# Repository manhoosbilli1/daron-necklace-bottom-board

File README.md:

# Daron_necklace_bottom

Bottom half of wearable LED necklace - power, haptic, USB-C charging

## At a Glance

- **Status**: Routed
- **Board size**: 20 x 20 mm
- **Layers**: 2
- **Components**: 42
- **Key ICs**:
  - U1: MCP73831-2-MC
  - U2: FH35C-11S-0.3SHW(50)_C7427016
  - U3: TPS63070RNMR
  - U7: DRV2605LDGS

## Schematic

Full PDF: [reports/schematic.pdf](reports/schematic.pdf)

## Component Roles

- **TPS63070RNMR** (U3) - buck-boost regulator (3.3 V output); handles wide LiPo voltage swing
- **DRV2605LDGS** (U7) - haptic motor driver for tactile feedback
- **MCP73831-2-MC** (U1) - single-cell LiPo charger
- **AO3401A** (Q1) - P-channel MOSFET for power switching / load enable
- **DMG3414U** (Q3) - N-channel MOSFET (companion to Q1 for full PowerPath)
- **FH35C-11S-0.3SHW** (U2) - 0.3 mm-pitch FPC connector for the top-board flex link
- **TC-005** (USB1) - micro USB-C receptacle (compact variant)
- **SP0503BAHT** (D1) - 3-line ESD protection on USB data lines
- **KT-0603R** (D3) - status LED

> Companion to the top-board (LED-driving half). The top board handles the addressable LED chain; this board handles power, charging, haptics.

## PCB

**Top copper**

**Bottom copper**

## Bill of Materials

| Refs | Value | Footprint | Qty | MPN | LCSC |
|------|-------|-----------|----:|-----|------|
| C1 | 47uF | PCM_JLCPCB:C_0805 | 1 |  | [C16780](https://www.lcsc.com/product-detail/_C16780.html) |
| C2,C8-C10,C15 | 100nF | PCM_JLCPCB:C_0402 | 5 |  | [C1525](https://www.lcsc.com/product-detail/_C1525.html) |
| C3,C4,C16 | 10uF | PCM_JLCPCB:C_0805 | 3 |  | [C15850](https://www.lcsc.com/product-detail/_C15850.html) |
| C5-C7 | 22uF | PCM_JLCPCB:C_0805 | 3 |  | [C45783](https://www.lcsc.com/product-detail/_C45783.html) |
| C11,C17 | 4.7uF | Capacitor_SMD:C_0402_1005Metric | 2 |  |  |
| C21,C22 | 1uF | Capacitor_SMD:C_0402_1005Metric | 2 |  |  |
| D1 | SP0503BAHT | Package_SON:WSON-6-1EP_2x2mm_P0.65mm_EP1x1.6mm | 1 |  |  |
| D2 | White | PCM_JLCPCB:D_0603 | 1 |  | [C2290](https://www.lcsc.com/product-detail/_C2290.html) |
| D3 | KT-0603R | LED_SMD:LED_0201_0603Metric | 1 |  |  |
| D4 | B5819W | Diode_SMD:D_0603_1608Metric | 1 |  |  |
| J2,J4 | Conn_01x02 | Connector_Wire:SolderWire-0.1sqmm_1x02_P3.6mm_D0.4mm_OD1mm | 2 |  |  |
| L2 | 1.5uH | Inductor_SMD:L_Coilcraft_XAL4020-XXX | 1 |  |  |
| Q1 | AO3401A | PCM_JLCPCB:Q_SOT-23 | 1 |  | [C15127](https://www.lcsc.com/product-detail/_C15127.html) |
| Q3 | DMG3414U | Package_TO_SOT_SMD:SOT-23 | 1 |  |  |
| R1 | 470kΩ | PCM_JLCPCB:R_0402 | 1 |  | [C25790](https://www.lcsc.com/product-detail/_C25790.html) |
| R2 | 150kΩ | PCM_JLCPCB:R_0402 | 1 |  | [C25755](https://www.lcsc.com/product-detail/_C25755.html) |
| R3,R4 | 5.1kΩ | PCM_JLCPCB:R_0402 | 2 |  | [C25905](https://www.lcsc.com/product-detail/_C25905.html) |
| R5 | 2.2kΩ | PCM_JLCPCB:R_0402 | 1 |  | [C25879](https://www.lcsc.com/product-detail/_C25879.html) |
| R6,R20 | 2.2k | Resistor_SMD:R_0402_1005Metric | 2 |  |  |
| R11 | 10kΩ | PCM_JLCPCB:R_0402 | 1 |  | [C25744](https://www.lcsc.com/product-detail/_C25744.html) |
| R13 | 1k | Resistor_SMD:R_0402_1005Metric | 1 |  |  |
| R14 | 10k | Resistor_SMD:R_0402_1005Metric | 1 |  |  |
| R18 | 100k | Resistor_SMD:R_0402_1005Metric | 1 |  |  |
| R19 | 100kΩ | PCM_JLCPCB:R_0402 | 1 |  | [C25741](https://www.lcsc.com/product-detail/_C25741.html) |
| U1 | MCP73831-2-MC | Package_DFN_QFN:DFN-8-1EP_3x2mm_P0.5mm_EP1.7x1.4mm | 1 |  |  |
| U2 | FH35C-11S-0.3SHW(50)_C7427016 | FH35C_11S_0_3SHW_50_:FPC-SMD_FH35C-11S-0.3SHW | 1 |  |  |
| U3 | TPS63070RNMR | TPS63070RNMR:VREG_TPS63070RNMR | 1 |  |  |
| U7 | DRV2605LDGS | Package_SO:VSSOP-10_3x3mm_P0.5mm | 1 |  |  |
| USB1 | TC-005_C6332285 | usbc:USB-C-SMD_TC-005 | 1 |  |  |

_17 of 29 line items don't have an LCSC code in the schematic - search [LCSC](https://www.lcsc.com/) or [JLC parts search](https://jlcsearch.tscircuit.com/) by MPN or footprint when sourcing._

## Files

- `Daron_necklace_bottom.kicad_pro` - KiCad project
- `Daron_necklace_bottom.kicad_sch` - schematic source
- `Daron_necklace_bottom.kicad_pcb` - PCB layout source
- `reports/schematic.pdf` - full schematic (printable)
- `reports/bom.csv` - bill of materials
- `reports/pcb-top.svg`, `reports/pcb-bottom.svg` - copper artwork
- `reports/board-stats.json` - KiCad-generated board statistics

---

_Renders and metadata auto-generated by `Backup-KiCadProject.ps1` using KiCad 10.0._

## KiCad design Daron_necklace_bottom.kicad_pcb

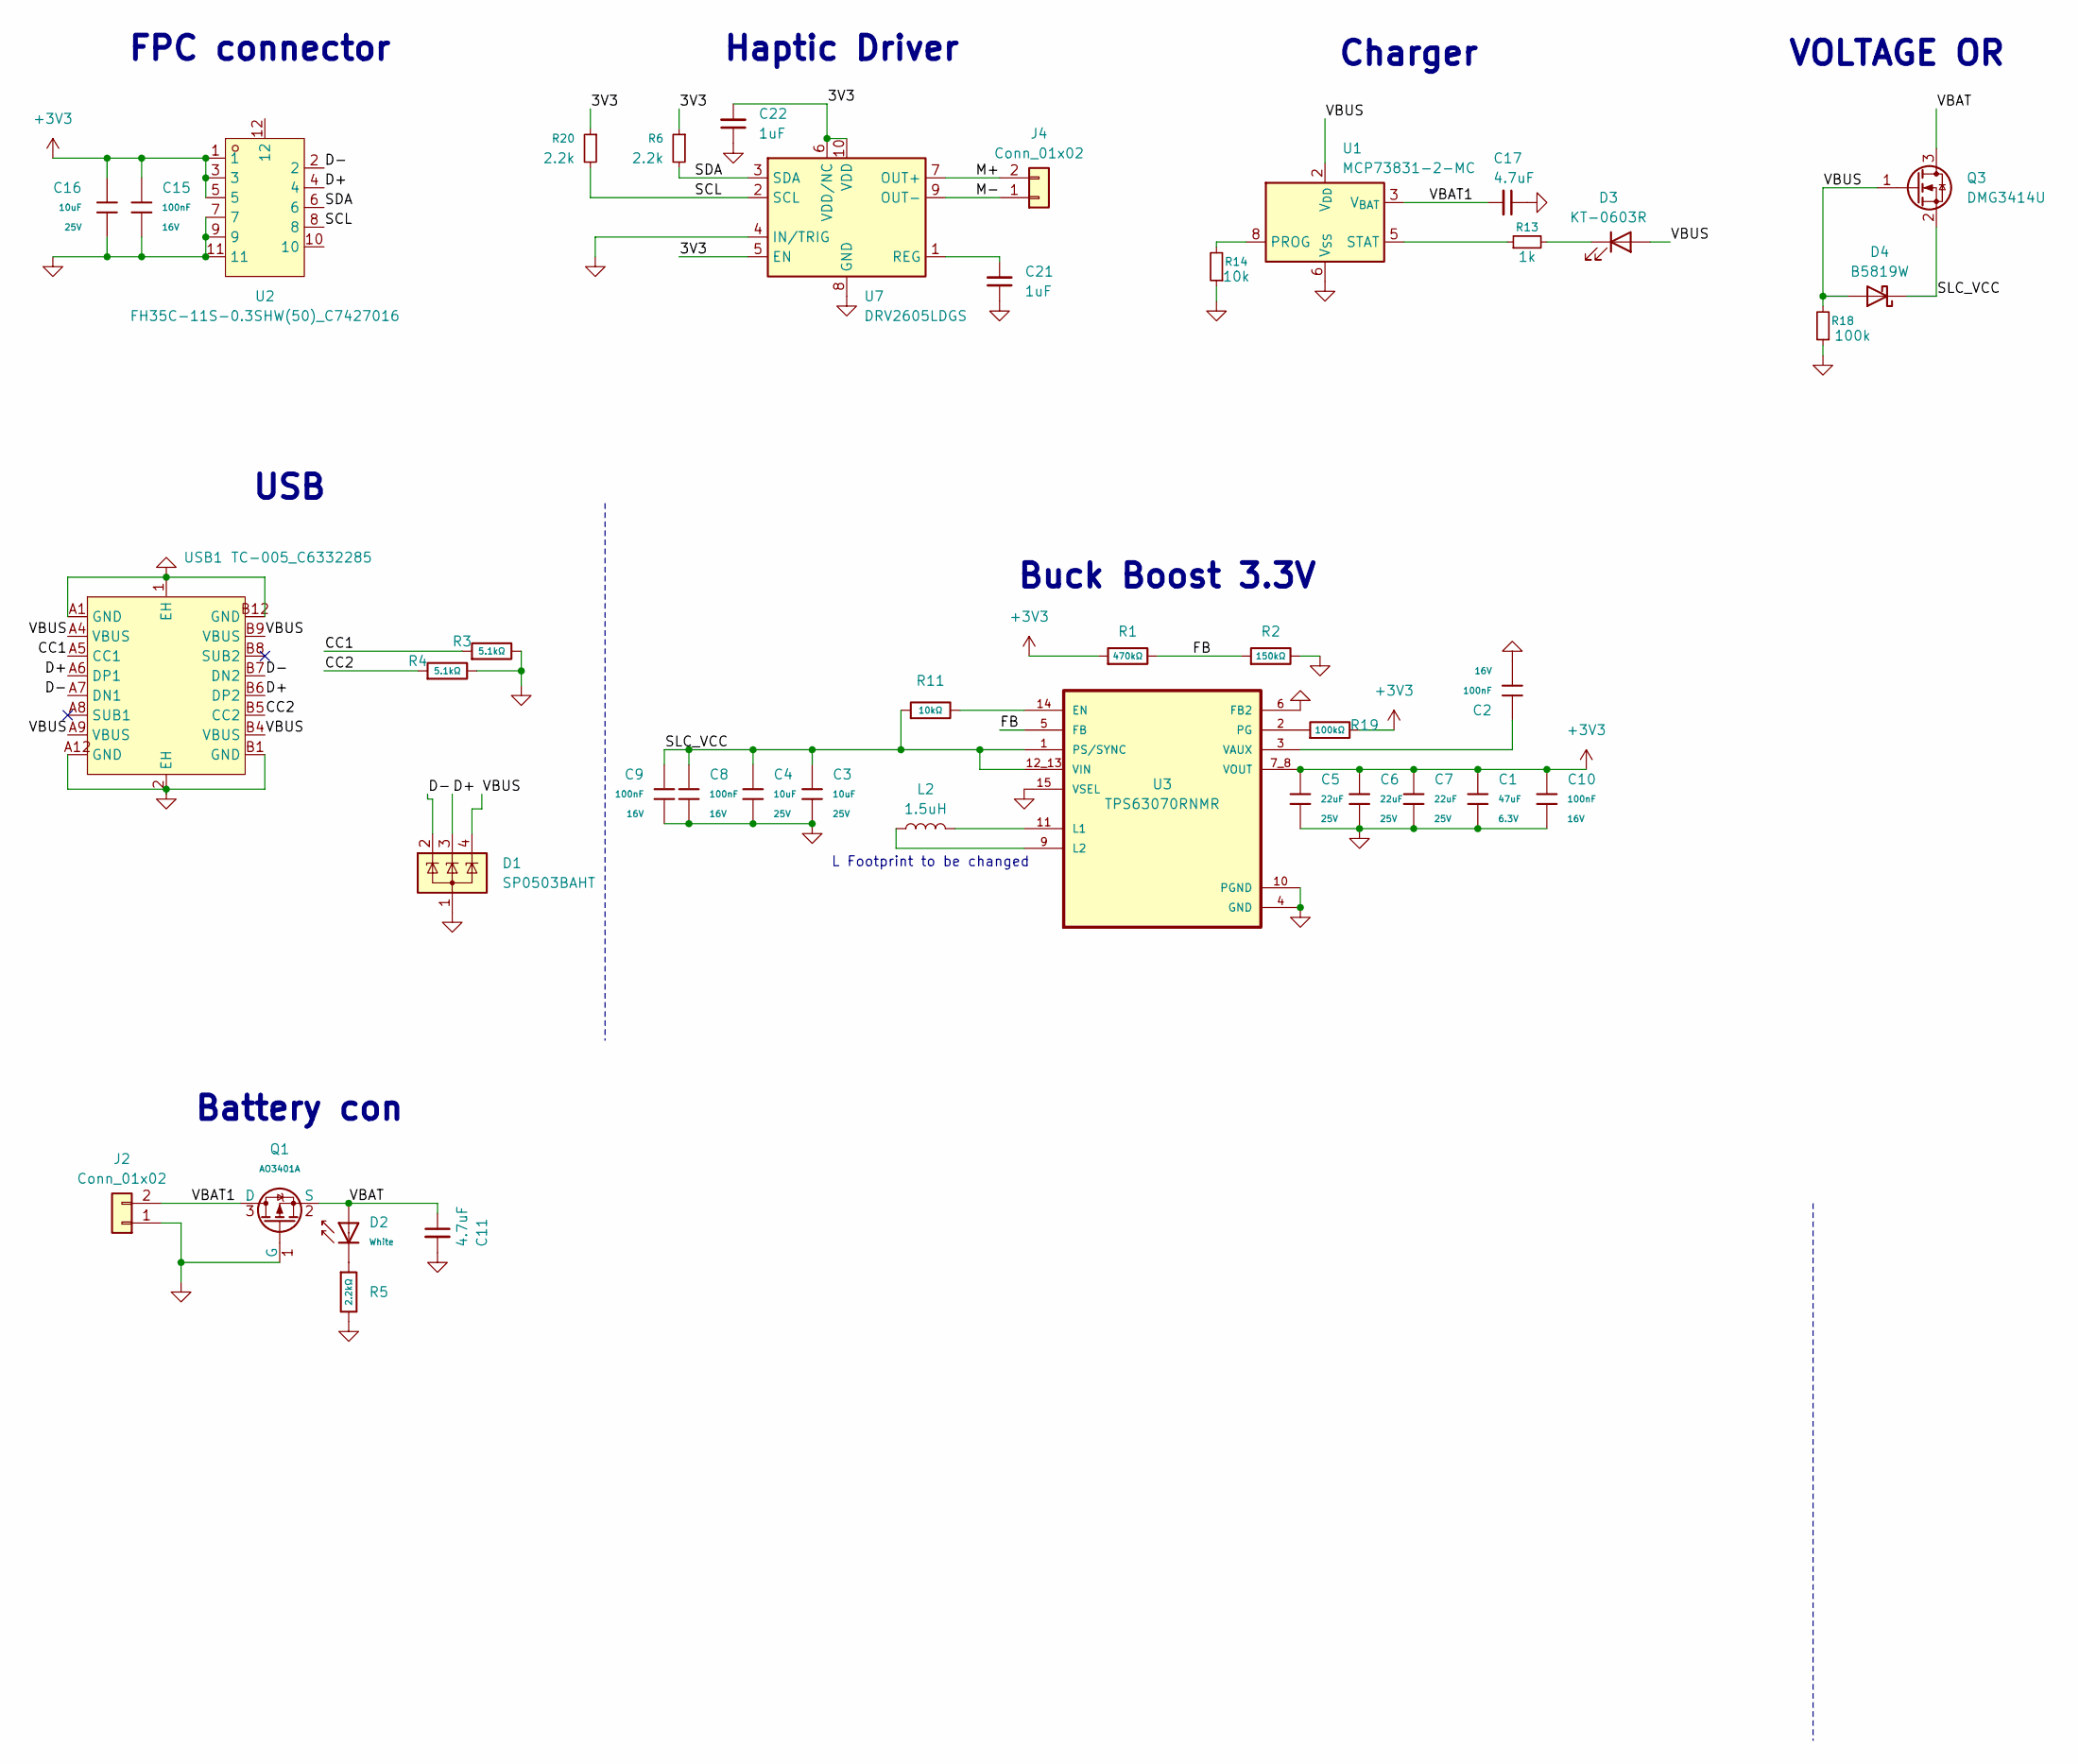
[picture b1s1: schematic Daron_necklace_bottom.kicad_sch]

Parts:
C1: 47uF; C_0805; Voltage Rated 6.3V; Tolerance ±20%; Part CL21A476MQYNNNE; LCSC C16780
C2, C8, C9, C10, C15: 100nF; C_0402; Voltage Rated 16V; Tolerance ±10%; Part CL05B104KO5NNNC; LCSC C1525
C3, C4, C16: 10uF; C_0805; Voltage Rated 25V; Tolerance ±10%; Part CL21A106KAYNNNE; LCSC C15850
C5, C6, C7: 22uF; C_0805; Voltage Rated 25V; Tolerance ±20%; Part CL21A226MAQNNNE; LCSC C45783
C11, C17: 4.7uF; C_0402_1005Metric
C21, C22: 1uF; C_0402_1005Metric
D1: SP0503BAHT; WSON-6-1EP_2x2mm_P0.65mm_EP1x1.6mm
D2: White; D_0603; Part KT-0603W; LCSC C2290
D3: KT-0603R; LED_0201_0603Metric
D4: B5819W; D_0603_1608Metric
J2, J4: Conn_01x02; SolderWire-0.1sqmm_1x02_P3.6mm_D0.4mm_OD1mm
L2: 1.5uH; L_Coilcraft_XAL4020-XXX
Q1: AO3401A; Q_SOT-23; Part AO3401A; LCSC C15127
Q3: DMG3414U; SOT-23
R1: 470kΩ; R_0402; Overload Voltage (Max) 50V; Tolerance ±1%; Part 0402WGF4703TCE; LCSC C25790
R2: 150kΩ; R_0402; Overload Voltage (Max) 50V; Tolerance ±1%; Part 0402WGF1503TCE; LCSC C25755
R3, R4: 5.1kΩ; R_0402; Overload Voltage (Max) 50V; Tolerance ±1%; Part 0402WGF5101TCE; LCSC C25905
R5: 2.2kΩ; R_0402; Overload Voltage (Max) 50V; Tolerance ±1%; Part 0402WGF2201TCE; LCSC C25879
R6, R20: 2.2k; R_0402_1005Metric
R11: 10kΩ; R_0402; Overload Voltage (Max) 50V; Tolerance ±1%; Part 0402WGF1002TCE; LCSC C25744
R13: 1k; R_0402_1005Metric
R14: 10k; R_0402_1005Metric
R18: 100k; R_0402_1005Metric
R19: 100kΩ; R_0402; Overload Voltage (Max) 50V; Tolerance ±1%; Part 0402WGF1003TCE; LCSC C25741
U1: MCP73831-2-MC; DFN-8-1EP_3x2mm_P0.5mm_EP1.7x1.4mm
U2: FH35C-11S-0.3SHW(50)_C7427016; FPC-SMD_FH35C-11S-0.3SHW; LCSC Part C7427016
U3: TPS63070RNMR; VREG_TPS63070RNMR
U7: DRV2605LDGS; VSSOP-10_3x3mm_P0.5mm
USB1: TC-005_C6332285; USB-C-SMD_TC-005; LCSC Part C6332285

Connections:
+3V3: C1.1, C5.1, C6.1, C7.1, C10.1, C15.1, C16.1, R1.1, R19.2, U2.1, U2.3, U2.5, U3.7_8 (VOUT)
/3V3: C22.2, R6.1, R20.1, U7.5 (EN), U7.6 (VDD/NC), U7.10 (VDD)
/CC1: R3.1, USB1.A5 (CC1)
/CC2: R4.1, USB1.B5 (CC2)
/D+: D1.3 (K), U2.4, USB1.A6 (DP1), USB1.B6 (DP2)
/D-: D1.2 (K), U2.2, USB1.A7 (DN1), USB1.B7 (DN2)
/FB: R1.2, R2.1, U3.5 (FB)
/M+: J4.2, U7.7 (OUT+)
/M-: J4.1, U7.9 (OUT-)
/SCL: R20.2, U2.8, U7.2 (SCL)
/SDA: R6.2, U2.6, U7.3 (SDA)
/SLC_VCC: C3.1, C4.1, C8.1, C9.1, D4.1 (K), Q3.2 (S), R11.1, U3.1 (PS/SYNC), U3.12_13 (VIN)
/VBAT: C11.1, D2.2, Q1.2 (S), Q3.3 (D)
/VBAT1: C17.2, J2.2, Q1.3 (D), U1.3 (V_{BAT}), U1.4 (V_{BAT})
/VBUS: D1.4 (K), D3.2 (A), D4.2 (A), Q3.1 (G), R18.2, U1.1 (V_{DD}), U1.2 (V_{DD}), USB1.A4 (VBUS), USB1.A9 (VBUS), USB1.B4 (VBUS), USB1.B9 (VBUS)
GND: C1.2, C2.2, C3.2, C4.2, C5.2, C6.2, C7.2, C8.2, C9.2, C10.2, C11.2, C15.2, C16.2, C17.1, C21.1, C22.1, D1.1 (A), J2.1, Q1.1 (G), R2.2, R3.2, R4.2, R5.2, R14.1, R18.1, U1.6 (V_{SS}), U2.7, U2.9, U2.11, U3.4 (GND), U3.6 (FB2), U3.10 (PGND), U3.15 (VSEL), U7.4 (IN/TRIG), U7.8 (GND), USB1.1 (EH), USB1.2 (EH), USB1.A1 (GND), USB1.A12 (GND), USB1.B1 (GND), USB1.B12 (GND)
unnamed: D2.1, R5.1
unnamed: D3.1 (K), R13.2
unnamed: R14.2, U1.8 (PROG)
unnamed: R13.1, U1.5 (STAT)
unnamed: R11.2, U3.14 (EN)
unnamed: L2.2, U3.11 (L1)
unnamed: L2.1, U3.9 (L2)
unnamed: R19.1, U3.2 (PG)
unnamed: C2.1, U3.3 (VAUX)
unnamed: C21.2, U7.1 (REG)

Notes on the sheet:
Battery con
Charger
VOLTAGE OR
Buck Boost 3.3V
USB
L Footprint to be changed
FPC connector
Haptic Driver

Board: 2 copper layers, 42 parts (26 on the bottom side), 26 nets, no tracks yet.

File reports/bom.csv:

"Refs","Value","Footprint","Qty","Description","Mfr","MPN","LCSC"
"C1","47uF","PCM_JLCPCB:C_0805","1","6.3V 47uF X5R ±20% 0805 Multilayer Ceramic Capacitors MLCC - SMD/SMT ROHS","Samsung Electro-Mechanics","","C16780"
"C2,C8-C10,C15","100nF","PCM_JLCPCB:C_0402","5","16V 100nF X7R ±10% 0402 Multilayer Ceramic Capacitors MLCC - SMD/SMT ROHS","Samsung Electro-Mechanics","","C1525"
"C3,C4,C16","10uF","PCM_JLCPCB:C_0805","3","25V 10uF X5R ±10% 0805 Multilayer Ceramic Capacitors MLCC - SMD/SMT ROHS","Samsung Electro-Mechanics","","C15850"
"C5-C7","22uF","PCM_JLCPCB:C_0805","3","25V 22uF X5R ±20% 0805 Multilayer Ceramic Capacitors MLCC - SMD/SMT ROHS","Samsung Electro-Mechanics","","C45783"
"C11,C17","4.7uF","Capacitor_SMD:C_0402_1005Metric","2","Unpolarized capacitor, small symbol","","",""
"C21,C22","1uF","Capacitor_SMD:C_0402_1005Metric","2","Unpolarized capacitor, small symbol","","",""
"D1","SP0503BAHT","Package_SON:WSON-6-1EP_2x2mm_P0.65mm_EP1x1.6mm","1","TVS Diode Array, 5.5V Standoff, 3 Channels, SOT-143 package","","",""
"D2","White","PCM_JLCPCB:D_0603","1","White 0603 LED Indication - Discrete ROHS","Hubei KENTO Elec","","C2290"
"D3","KT-0603R","LED_SMD:LED_0201_0603Metric","1","Light emitting diode","","",""
"D4","B5819W","Diode_SMD:D_0603_1608Metric","1","Schottky diode","","",""
"J2,J4","Conn_01x02","Connector_Wire:SolderWire-0.1sqmm_1x02_P3.6mm_D0.4mm_OD1mm","2","Generic connector, single row, 01x02, script generated (kicad-library-utils/schlib/autogen/connector/)","","",""
"L2","1.5uH","Inductor_SMD:L_Coilcraft_XAL4020-XXX","1","Inductor","","",""
"Q1","AO3401A","PCM_JLCPCB:Q_SOT-23","1","30V 4A 44mΩ@10V,4.3A 1.4W 1.3V@250uA 1 Piece P-Channel SOT-23 MOSFETs ROHS","Alpha & Omega Semicon","","C15127"
"Q3","DMG3414U","Package_TO_SOT_SMD:SOT-23","1","4.2A Id, 20V Vds, N-Channel MOSFET, SOT-23","","",""
"R1","470kΩ","PCM_JLCPCB:R_0402","1","62.5mW Thick Film Resistors 50V ±100ppm/°C ±1% 470kΩ 0402 Chip Resistor - Surface Mount ROHS","UNI-ROYAL(Uniroyal Elec)","","C25790"
"R2","150kΩ","PCM_JLCPCB:R_0402","1","62.5mW Thick Film Resistors 50V ±100ppm/°C ±1% 150kΩ 0402 Chip Resistor - Surface Mount ROHS","UNI-ROYAL(Uniroyal Elec)","","C25755"
"R3,R4","5.1kΩ","PCM_JLCPCB:R_0402","2","62.5mW Thick Film Resistors 50V ±100ppm/°C ±1% 5.1kΩ 0402 Chip Resistor - Surface Mount ROHS","UNI-ROYAL(Uniroyal Elec)","","C25905"
"R5","2.2kΩ","PCM_JLCPCB:R_0402","1","62.5mW Thick Film Resistors 50V ±100ppm/°C ±1% 2.2kΩ 0402 Chip Resistor - Surface Mount ROHS","UNI-ROYAL(Uniroyal Elec)","","C25879"
"R6,R20","2.2k","Resistor_SMD:R_0402_1005Metric","2","Resistor, small symbol","","",""
"R11","10kΩ","PCM_JLCPCB:R_0402","1","62.5mW Thick Film Resistors 50V ±100ppm/°C ±1% 10kΩ 0402 Chip Resistor - Surface Mount ROHS","UNI-ROYAL(Uniroyal Elec)","","C25744"
"R13","1k","Resistor_SMD:R_0402_1005Metric","1","Resistor, small symbol","","",""
"R14","10k","Resistor_SMD:R_0402_1005Metric","1","Resistor, small symbol","","",""
"R18","100k","Resistor_SMD:R_0402_1005Metric","1","Resistor, small symbol","","",""
"R19","100kΩ","PCM_JLCPCB:R_0402","1","62.5mW Thick Film Resistors 50V ±100ppm/°C ±1% 100kΩ 0402 Chip Resistor - Surface Mount ROHS","UNI-ROYAL(Uniroyal Elec)","","C25741"
"U1","MCP73831-2-MC","Package_DFN_QFN:DFN-8-1EP_3x2mm_P0.5mm_EP1.7x1.4mm","1","Single cell, Li-Ion/Li-Po charge management controller, 4.20V, Tri-State Status Output, in DFN-8 package","","",""
"U2","FH35C-11S-0.3SHW(50)_C7427016","FH35C_11S_0_3SHW_50_:FPC-SMD_FH35C-11S-0.3SHW","1","","","",""
"U3","TPS63070RNMR","TPS63070RNMR:VREG_TPS63070RNMR","1","","","",""
"U7","DRV2605LDGS","Package_SO:VSSOP-10_3x3mm_P0.5mm","1","Haptic driver for LRAs and ERMs with effect library, 2-5.2V, VSSOP-10","","",""
"USB1","TC-005_C6332285","usbc:USB-C-SMD_TC-005","1","","","",""

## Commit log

2026-05-18 Update backup artifacts
2026-05-18 Enrich README: schematic PNG, component roles, BOM table
